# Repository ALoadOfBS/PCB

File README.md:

# PCB
A PCB Design as per the ai03 pcb guide
This build was Designed and Created by Benjamin Sanchez

For a list of everything that you need for the build look at Partslist.txt

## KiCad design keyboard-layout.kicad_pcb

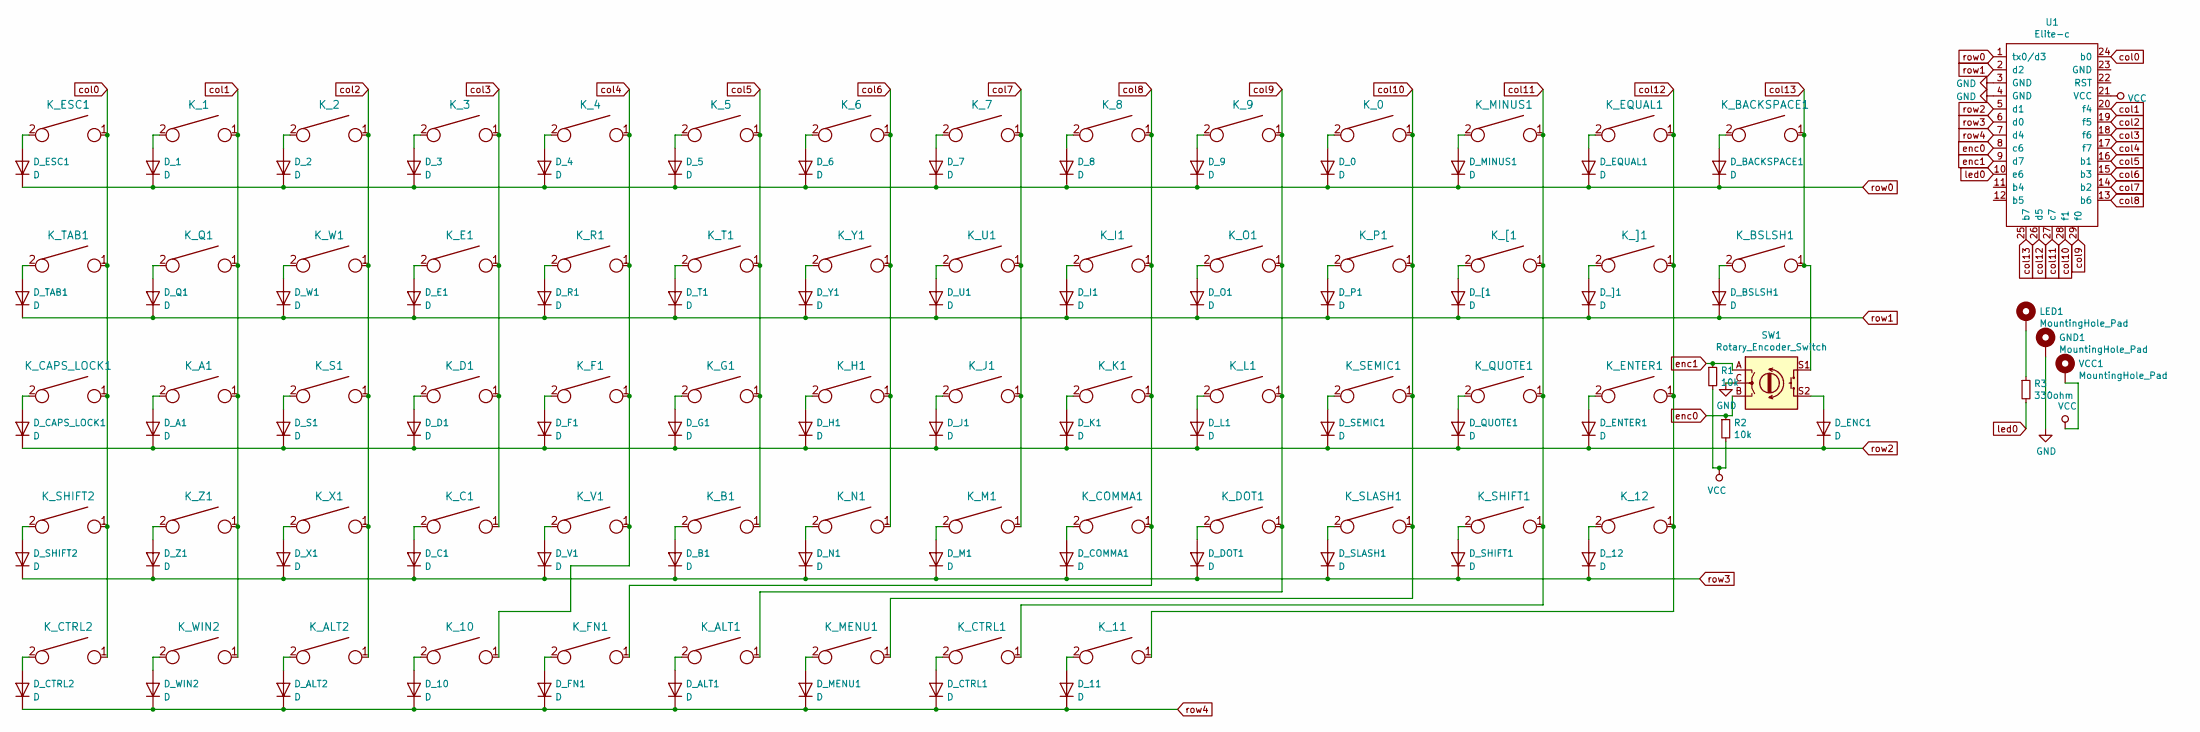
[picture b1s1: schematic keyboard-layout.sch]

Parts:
D_0, D_1, D_2, D_3, D_4, D_5, D_6, D_7, D_8, D_9, D_10, D_11, D_12: D; D_SOD123_axial
D_A1: D; D_SOD123_axial
D_ALT1, D_ALT2: D; D_SOD123_axial
D_B1: D; D_SOD123_axial
D_BACKSPACE1: D; D_SOD123_axial
D_BSLSH1: D; D_SOD123_axial
D_C1: D; D_SOD123_axial
D_CAPS_LOCK1: D; D_SOD123_axial
D_COMMA1: D; D_SOD123_axial
D_CTRL1, D_CTRL2: D; D_SOD123_axial
D_D1: D; D_SOD123_axial
D_DOT1: D; D_SOD123_axial
D_E1: D; D_SOD123_axial
D_ENC1: D; D_SOD123_axial
D_ENTER1: D; D_SOD123_axial
D_EQUAL1: D; D_SOD123_axial
D_ESC1: D; D_SOD123_axial
D_F1: D; D_SOD123_axial
D_FN1: D; D_SOD123_axial
D_G1: D; D_SOD123_axial
D_H1: D; D_SOD123_axial
D_I1: D; D_SOD123_axial
D_J1: D; D_SOD123_axial
D_K1: D; D_SOD123_axial
D_L1: D; D_SOD123_axial
D_M1: D; D_SOD123_axial
D_MENU1: D; D_SOD123_axial
D_MINUS1: D; D_SOD123_axial
D_N1: D; D_SOD123_axial
D_O1: D; D_SOD123_axial
D_P1: D; D_SOD123_axial
D_Q1: D; D_SOD123_axial
D_QUOTE1: D; D_SOD123_axial
D_R1: D; D_SOD123_axial
D_S1: D; D_SOD123_axial
D_SEMIC1: D; D_SOD123_axial
D_SHIFT1, D_SHIFT2: D; D_SOD123_axial
D_SLASH1: D; D_SOD123_axial
D_T1: D; D_SOD123_axial
D_TAB1: D; D_SOD123_axial
D_U1: D; D_SOD123_axial
D_V1: D; D_SOD123_axial
D_W1: D; D_SOD123_axial
D_WIN2: D; D_SOD123_axial
D_X1: D; D_SOD123_axial
D_Y1: D; D_SOD123_axial
D_Z1: D; D_SOD123_axial
D_[1: D; D_SOD123_axial
D_]1: D; D_SOD123_axial
GND1: MountingHole_Pad; SolderWirePad_1x01_Drill0.8mm
K_0, K_1, K_2, K_3, K_4, K_5, K_6, K_7, K_8, K_9, K_11, K_12: KEYSW; MX-1U-NoLED
K_10: KEYSW; MX-6.25U-NoLED
K_A1: KEYSW; MX-1U-NoLED
K_ALT1, K_ALT2: KEYSW; MX-1.25U-NoLED
K_B1: KEYSW; MX-1U-NoLED
K_BACKSPACE1: KEYSW; MX-2U-NoLED
K_BSLSH1: KEYSW; MX-1.5U-NoLED
K_C1: KEYSW; MX-1U-NoLED
K_CAPS_LOCK1: KEYSW; MX-1.75U-NoLED
K_COMMA1: KEYSW; MX-1U-NoLED
K_CTRL1, K_CTRL2: KEYSW; MX-1.25U-NoLED
K_D1: KEYSW; MX-1U-NoLED
K_DOT1: KEYSW; MX-1U-NoLED
K_E1: KEYSW; MX-1U-NoLED
K_ENTER1: KEYSW; MX-2.25U-NoLED
K_EQUAL1: KEYSW; MX-1U-NoLED
K_ESC1: KEYSW; MX-1U-NoLED
K_F1: KEYSW; MX-1U-NoLED
K_FN1: KEYSW; MX-1.25U-NoLED
K_G1: KEYSW; MX-1U-NoLED
K_H1: KEYSW; MX-1U-NoLED
K_I1: KEYSW; MX-1U-NoLED
K_J1: KEYSW; MX-1U-NoLED
K_K1: KEYSW; MX-1U-NoLED
K_L1: KEYSW; MX-1U-NoLED
K_M1: KEYSW; MX-1U-NoLED
K_MENU1: KEYSW; MX-1.25U-NoLED
K_MINUS1: KEYSW; MX-1U-NoLED
K_N1: KEYSW; MX-1U-NoLED
K_O1: KEYSW; MX-1U-NoLED
K_P1: KEYSW; MX-1U-NoLED
K_Q1: KEYSW; MX-1U-NoLED
K_QUOTE1: KEYSW; MX-1U-NoLED
K_R1: KEYSW; MX-1U-NoLED
K_S1: KEYSW; MX-1U-NoLED
K_SEMIC1: KEYSW; MX-1U-NoLED
K_SHIFT1: KEYSW; MX-2.75U-NoLED
K_SHIFT2: KEYSW; MX-2.25U-NoLED
K_SLASH1: KEYSW; MX-1U-NoLED
K_T1: KEYSW; MX-1U-NoLED
K_TAB1: KEYSW; MX-1.5U-NoLED
K_U1: KEYSW; MX-1U-NoLED
K_V1: KEYSW; MX-1U-NoLED
K_W1: KEYSW; MX-1U-NoLED
K_WIN2: KEYSW; MX-1.25U-NoLED
K_X1: KEYSW; MX-1U-NoLED
K_Y1: KEYSW; MX-1U-NoLED
K_Z1: KEYSW; MX-1U-NoLED
K_[1: KEYSW; MX-1U-NoLED
K_]1: KEYSW; MX-1U-NoLED
LED1: MountingHole_Pad; SolderWirePad_1x01_Drill0.8mm
R1, R2: 10k; R_Axial_DIN0207_L6.3mm_D2.5mm_P7.62mm_Horizontal
R3: 330ohm; R_Axial_DIN0207_L6.3mm_D2.5mm_P7.62mm_Horizontal
SW1: Rotary_Encoder_Switch; RotaryEncoder_Alps_EC11E-Switch_Vertical_H20mm
U1: Elite-c; Elite-C-castellated-29pin-holes
VCC1: MountingHole_Pad; SolderWirePad_1x01_Drill0.8mm

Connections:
GND: GND1.1, SW1.C, U1.3 (GND), U1.4 (GND); also elsewhere on the board
unnamed: D_0.2 (A), K_0.2
unnamed: D_1.2 (A), K_1.2
unnamed: D_2.2 (A), K_2.2
unnamed: D_3.2 (A), K_3.2
unnamed: D_4.2 (A), K_4.2
unnamed: D_5.2 (A), K_5.2
unnamed: D_6.2 (A), K_6.2
unnamed: D_7.2 (A), K_7.2
unnamed: D_8.2 (A), K_8.2
unnamed: D_9.2 (A), K_9.2
unnamed: D_10.2 (A), K_10.2
unnamed: D_11.2 (A), K_11.2
unnamed: D_12.2 (A), K_12.2
unnamed: D_A1.2 (A), K_A1.2
unnamed: D_ALT1.2 (A), K_ALT1.2
unnamed: D_ALT2.2 (A), K_ALT2.2
unnamed: D_B1.2 (A), K_B1.2
unnamed: D_BACKSPACE1.2 (A), K_BACKSPACE1.2
unnamed: D_BSLSH1.2 (A), K_BSLSH1.2
unnamed: D_C1.2 (A), K_C1.2
unnamed: D_CAPS_LOCK1.2 (A), K_CAPS_LOCK1.2
unnamed: D_COMMA1.2 (A), K_COMMA1.2
unnamed: D_CTRL1.2 (A), K_CTRL1.2
unnamed: D_CTRL2.2 (A), K_CTRL2.2
unnamed: D_D1.2 (A), K_D1.2
unnamed: D_DOT1.2 (A), K_DOT1.2
unnamed: D_E1.2 (A), K_E1.2
unnamed: D_ENC1.2 (A), SW1.S2
unnamed: D_ENTER1.2 (A), K_ENTER1.2
unnamed: D_EQUAL1.2 (A), K_EQUAL1.2
unnamed: D_ESC1.2 (A), K_ESC1.2
unnamed: D_F1.2 (A), K_F1.2
unnamed: D_FN1.2 (A), K_FN1.2
unnamed: D_G1.2 (A), K_G1.2
unnamed: D_H1.2 (A), K_H1.2
unnamed: D_I1.2 (A), K_I1.2
unnamed: D_J1.2 (A), K_J1.2
unnamed: D_K1.2 (A), K_K1.2
unnamed: D_L1.2 (A), K_L1.2
unnamed: D_M1.2 (A), K_M1.2
unnamed: D_MENU1.2 (A), K_MENU1.2
unnamed: D_MINUS1.2 (A), K_MINUS1.2
unnamed: D_N1.2 (A), K_N1.2
unnamed: D_O1.2 (A), K_O1.2
unnamed: D_P1.2 (A), K_P1.2
unnamed: D_Q1.2 (A), K_Q1.2
unnamed: D_QUOTE1.2 (A), K_QUOTE1.2
unnamed: D_R1.2 (A), K_R1.2
unnamed: D_S1.2 (A), K_S1.2
unnamed: D_SEMIC1.2 (A), K_SEMIC1.2
unnamed: D_SHIFT1.2 (A), K_SHIFT1.2
unnamed: D_SHIFT2.2 (A), K_SHIFT2.2
unnamed: D_SLASH1.2 (A), K_SLASH1.2
unnamed: D_T1.2 (A), K_T1.2
unnamed: D_TAB1.2 (A), K_TAB1.2
unnamed: D_U1.2 (A), K_U1.2
unnamed: D_V1.2 (A), K_V1.2
unnamed: D_W1.2 (A), K_W1.2
unnamed: D_WIN2.2 (A), K_WIN2.2
unnamed: D_X1.2 (A), K_X1.2
unnamed: D_Y1.2 (A), K_Y1.2
unnamed: D_Z1.2 (A), K_Z1.2
unnamed: D_[1.2 (A), K_[1.2
unnamed: D_]1.2 (A), K_]1.2
unnamed 65: LED1.1, R3.1; also elsewhere on the board
VCC: R1.2, R2.2, U1.21 (VCC), VCC1.1; also elsewhere on the board
col0: K_CAPS_LOCK1.1, K_CTRL2.1, K_ESC1.1, K_SHIFT2.1, K_TAB1.1, U1.24 (b0)
col1: K_1.1, K_A1.1, K_Q1.1, K_WIN2.1, K_Z1.1, U1.20 (f4)
col2: K_2.1, K_ALT2.1, K_S1.1, K_W1.1, K_X1.1, U1.19 (f5)
col3: K_3.1, K_C1.1, K_D1.1, K_E1.1, U1.18 (f6)
col4: K_4.1, K_10.1, K_F1.1, K_R1.1, K_V1.1, U1.17 (f7)
col5: K_5.1, K_B1.1, K_G1.1, K_T1.1, U1.16 (b1)
col6: K_6.1, K_H1.1, K_N1.1, K_Y1.1, U1.15 (b3)
col7: K_7.1, K_J1.1, K_M1.1, K_U1.1, U1.14 (b2)
col8: K_8.1, K_COMMA1.1, K_FN1.1, K_I1.1, K_K1.1, U1.13 (b6)
col9: K_9.1, K_ALT1.1, K_DOT1.1, K_L1.1, K_O1.1, U1.29 (f0)
col10: K_0.1, K_MENU1.1, K_P1.1, K_SEMIC1.1, K_SLASH1.1, U1.28 (f1)
col11: K_CTRL1.1, K_MINUS1.1, K_QUOTE1.1, K_SHIFT1.1, K_[1.1, U1.27 (c7)
col12: K_11.1, K_12.1, K_ENTER1.1, K_EQUAL1.1, K_]1.1, U1.26 (d5)
col13: K_BACKSPACE1.1, K_BSLSH1.1, SW1.S1, U1.25 (b7)
enc0: R2.1, SW1.B, U1.8 (c6)
enc1: R1.1, SW1.A, U1.9 (d7)
led0: R3.2, U1.10 (e6)
row0: D_0.1 (K), D_1.1 (K), D_2.1 (K), D_3.1 (K), D_4.1 (K), D_5.1 (K), D_6.1 (K), D_7.1 (K), D_8.1 (K), D_9.1 (K), D_BACKSPACE1.1 (K), D_EQUAL1.1 (K), D_ESC1.1 (K), D_MINUS1.1 (K), U1.1 (tx0/d3)
row1: D_BSLSH1.1 (K), D_E1.1 (K), D_I1.1 (K), D_O1.1 (K), D_P1.1 (K), D_Q1.1 (K), D_R1.1 (K), D_T1.1 (K), D_TAB1.1 (K), D_U1.1 (K), D_W1.1 (K), D_Y1.1 (K), D_[1.1 (K), D_]1.1 (K), U1.2 (d2)
row2: D_A1.1 (K), D_CAPS_LOCK1.1 (K), D_D1.1 (K), D_ENC1.1 (K), D_ENTER1.1 (K), D_F1.1 (K), D_G1.1 (K), D_H1.1 (K), D_J1.1 (K), D_K1.1 (K), D_L1.1 (K), D_QUOTE1.1 (K), D_S1.1 (K), D_SEMIC1.1 (K), U1.5 (d1)
row3: D_12.1 (K), D_B1.1 (K), D_C1.1 (K), D_COMMA1.1 (K), D_DOT1.1 (K), D_M1.1 (K), D_N1.1 (K), D_SHIFT1.1 (K), D_SHIFT2.1 (K), D_SLASH1.1 (K), D_V1.1 (K), D_X1.1 (K), D_Z1.1 (K), U1.6 (d0)
row4: D_10.1 (K), D_11.1 (K), D_ALT1.1 (K), D_ALT2.1 (K), D_CTRL1.1 (K), D_CTRL2.1 (K), D_FN1.1 (K), D_MENU1.1 (K), D_WIN2.1 (K), U1.7 (d4)

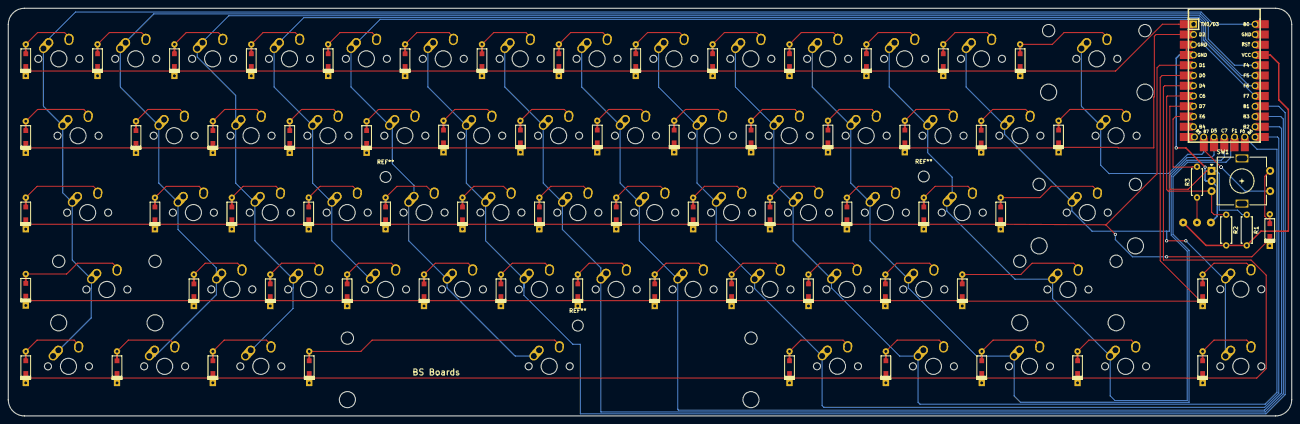
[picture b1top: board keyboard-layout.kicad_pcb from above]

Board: 2 copper layers, 318.0 x 101.0 mm, 135 parts (0 on the bottom side), 89 nets.

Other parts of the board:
GND: MountingHole_Pad; SolderWirePad_1x01_Drill0.8mm
LED: MountingHole_Pad; SolderWirePad_1x01_Drill0.8mm
VCC: MountingHole_Pad; SolderWirePad_1x01_Drill0.8mm

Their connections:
GND: GND.1; also elsewhere on the board
unnamed 65: LED.1; also elsewhere on the board
VCC: VCC.1; also elsewhere on the board

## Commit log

2020-02-24 Add submodules
2020-02-24 Create fp-info-cache
2020-02-24 Create fp-lib-table
2020-02-24 Create sym-lib-table
2020-03-10 Update fp-lib-table
2020-03-10 Create PCB60_endocer.sch-bak
2020-03-10 Update sym-lib-table
2020-03-10 Create LICENSE
2020-04-17 Update fp-info-cache
2020-04-17 Create keyboard-layout.kicad_pcb-bak
2020-04-17 Create keyboard-layout.sch-bak
2020-04-17 new file: Case Files/Case Files Ver 1(OLD)/Black Layer-k 4-5mm.dxf new file: Case Files/Case Files Ver 1(OLD)/Black Layer-k 4-5mm.eps new file: Case Files/Case Files Ver 1(OLD)/Clear Layer-k 1-5mm.dx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
2020-04-17 renamed: Case Files/Case Files Ver 2/Backplate.dxf -> Case Files/Case Files Ver 2(OLD)/Backplate.dxf renamed: Case Files/Case Files Ver 2/Backplate.eps -> Case Files/Case Files Ver 2(OLD)/Backplate.e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
2020-04-18 modified: Parts List.txt modified: README.md
2020-04-18 modified: Parts List.txt
2020-04-18 new file: Keymap Guide(how I have it set up).txt new file: QMK AND KEYMAP FILES/bsboards/Makefile new file: QMK AND KEYMAP FILES/bsboards/bsboards.c new file: QMK AND KEYMAP FILES/bsboards/bsboards.h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
2020-04-20 new file: JPGs/Case_model_1.jpg new file: JPGs/Case_model_2.jpg new file: JPGs/Case_model_guts.jpg new file: JPGs/Case_model_low_profile.jpg
